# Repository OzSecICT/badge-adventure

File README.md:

# OzSec 2024 Adventure Badge

This repo contains the code and KiCad files to design the OzSec 2024 badge. 

## Theme

The theme of this year's badge is 'Light The Badge' where the front of the badge has LEDs representing various cities. In the default mode it will be twinkly and randomly blink the LEDs. 

When you connect to the badge via a serial console, a text-based adventure RPG will be playable. Each city in the game is represented by an LED, and each city will have a quest that needs to be completed. 

Once you complete each city's quest, that LED will light up. You need to light up every city in order to unlock access to Wichita and change the RGB LED. Completing that ultimate quest will reveal a CTF flag and change the RGB LED to green. 

## Codebase

The badge is based on an ESP32-S3 using the Arduino framework. This repo is designed to be opened in VS Code with the PlatformIO extension. 

### Files

Brief overview of the files and what they do:

**include/config.hpp:**
- Tracks the currently developed version for use with updates over the web. 
- WiFi SSID and Password defaults.

**include/ozsec/update.hpp and src/ozsec/update.cpp:**
- Manages over the air updates.
- Triggered by holding boot button in `main.cpp`

**includes/ozsec/ble.hpp and src/ozsec/ble.hpp:**
- Bluetooth Low Energy config, searches for an advertisement from an OzSec 2023: S1M0N badge. Sets a variable once a badge advertisement is found and stops searching.

**includes/ozsec/lights.hpp and src/ozsec/lights.cpp:**
- Manages the LEDs and NeoPixel RGB LED
- `Lights::twinkle()` is the main function that is called by `Adventure::bgloop()` on the second core in `main.cpp` to twinkle the lights when not in the game.

**src/main.cpp:**
- Main arduino `setup()` and `loop()` functions that call other class functions. 
- Sets up buttons using the OneButton library.
- Manages persistent data and game/badge states using the Preferences library.

**includes/ozsec/buttons.hpp:**
- Centralized setup of the buttons using OneButton

**includes/ozsec/rooms.hpp:**
- Room configs for the text based adventure

**includes/ozsec/npcs.hpp:**
- NPC config for the text based adventure

**includes/ozsec/adventure.hpp and src/ozsec/adventure.cpp:**
- The main text based adventure game.
- Manages character and badge states, what lights are lit, flags unlocked, etc.

### Wi-Fi setup
You can either set the wifi credentials in `config.hpp` or you can launch into the text game and enter `wifi` command to set it on your badge specifically.

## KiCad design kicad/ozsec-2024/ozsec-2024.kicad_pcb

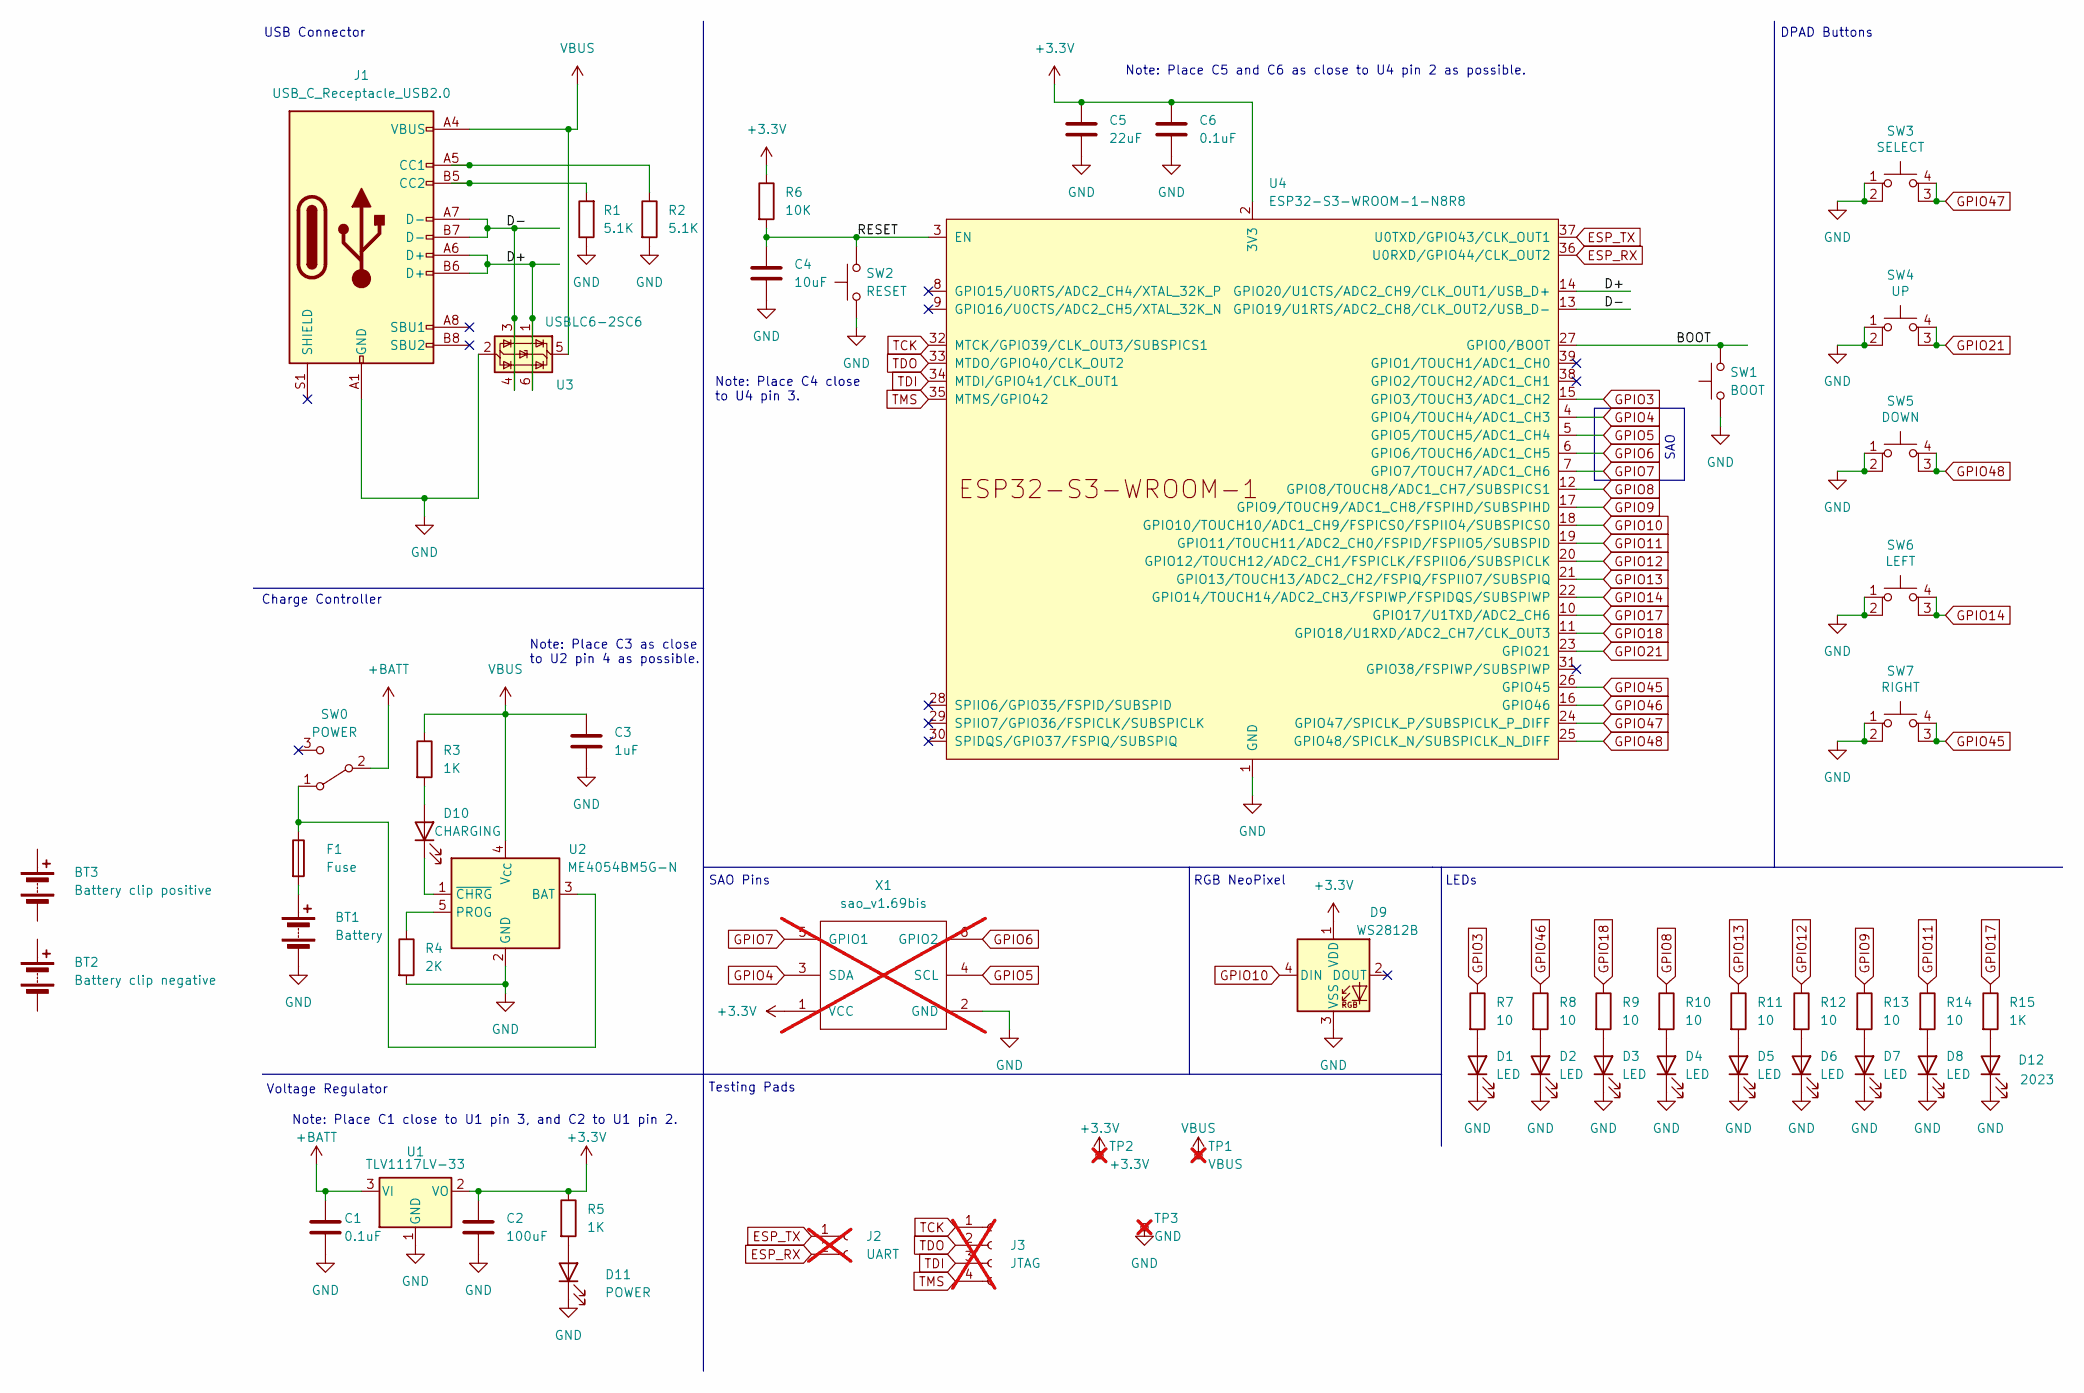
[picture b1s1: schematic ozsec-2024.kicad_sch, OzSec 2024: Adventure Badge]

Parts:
BT1: Battery; MY-AA-04_Silkscreen_Only; LCSC C2979179
BT2: Battery clip negative; MY-AA-04_Negative; LCSC C2979179
BT3: Battery clip positive; MY-AA-04_Positive; LCSC C2979179
C1, C6: 0.1uF; C_0402_1005Metric; LCSC C1525
C2: 100uF; C_1206_3216Metric; LCSC C15008
C3: 1uF; C_0402_1005Metric; LCSC C52923
C4: 10uF; C_0805_2012Metric; LCSC C15850
C5: 22uF; C_0805_2012Metric; LCSC C45783
D1, D2, D3, D4, D5, D6, D7, D8: LED; LED_0805_2012Metric_Pad1.15x1.40mm_HandSolder; LCSC C34499
D9: WS2812B; LED_WS2812B_PLCC4_5.0x5.0mm_P3.2mm; LCSC C2843785
D10: CHARGING; LED_0805_2012Metric_Pad1.15x1.40mm_HandSolder; LCSC C2296
D11: POWER; LED_0805_2012Metric_Pad1.15x1.40mm_HandSolder; LCSC C2297
D12: 2023; LED_0805_2012Metric_Pad1.15x1.40mm_HandSolder; LCSC C2297
F1: Fuse; Fuse_1206_3216Metric; LCSC C261957
J1: USB_C_Receptacle_USB2.0; USB_C_Receptacle_G-Switch_GT-USB-7010ASV; LCSC C2988369
J2: UART; PinHeader_1x02_P2.54mm_Vertical; not fitted
J3: JTAG; PinHeader_1x04_P2.54mm_Vertical; not fitted
R1, R2: 5.1K; R_0805_2012Metric; LCSC C27834
R3, R5, R15: 1K; R_0805_2012Metric_Pad1.20x1.40mm_HandSolder; LCSC C17513
R4: 2K; R_0805_2012Metric; LCSC C17604
R6: 10K; R_0805_2012Metric; LCSC C17414
R7, R8, R9, R10, R11, R12, R13, R14: 10; R_0805_2012Metric; LCSC C17415
SW0: POWER; SW_SPDT_PCM12; LCSC C431541
SW1: BOOT; SW_Push_1P1T_XKB_TS-1187A; LCSC C318884
SW2: RESET; SW_Push_1P1T_XKB_TS-1187A; LCSC C318884
SW3: SELECT; SW_SMD_TSC015XXXXXXX; LCSC C2888900
SW4: UP; SW_SMD_TSC015XXXXXXX; LCSC C2888900
SW5: DOWN; SW_SMD_TSC015XXXXXXX; LCSC C2888900
SW6: LEFT; SW_SMD_TSC015XXXXXXX; LCSC C2888900
SW7: RIGHT; SW_SMD_TSC015XXXXXXX; LCSC C2888900
TP1: VBUS; TestPoint_Pad_D1.5mm; not fitted
TP2: +3.3V; TestPoint_Pad_D1.5mm; not fitted
TP3: GND; TestPoint_Pad_1.5x1.5mm; not fitted
U1: TLV1117LV-33; SOT-223; LCSC C15578
U2: ME4054BM5G-N; TSOT-23-5; LCSC C478383
U3: USBLC6-2SC6; SOT-23-6; LCSC C2827654
U4: ESP32-S3-WROOM-1-N8R8; ESP32-S3-WROOM-1; LCSC C2913201
X1: sao_v1.69bis; Badgelife-SAOv169-BADGE-2x3; not fitted

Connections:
+3.3V: C2.1, C5.1, C6.1, D9.1 (VDD), R5.1, R6.1, TP2.1, U1.2 (VO), U1.4, U4.2 (3V3), X1.1 (VCC)
+BATT: C1.1, SW0.2 (B), U1.3 (VI)
/BOOT: SW1.2, U4.27 (GPIO0/BOOT)
/D+: J1.A6 (D+), J1.B6 (D+), U3.1 (I/O1), U3.6 (I/O1), U4.14 (GPIO20/U1CTS/ADC2_CH9/CLK_OUT1/USB_D+)
/D-: J1.A7 (D-), J1.B7 (D-), U3.3 (I/O2), U3.4 (I/O2), U4.13 (GPIO19/U1RTS/ADC2_CH8/CLK_OUT2/USB_D-)
/RESET: C4.1, R6.2, SW2.2, U4.3 (EN)
ESP_RX: J2.2, U4.36 (U0RXD/GPIO44/CLK_OUT2)
ESP_TX: J2.1, U4.37 (U0TXD/GPIO43/CLK_OUT1)
GND: BT1.2 (-), BT2.2 (-), C1.2, C2.2, C3.2, C4.2, C5.2, C6.2, D1.1 (K), D2.1 (K), D3.1 (K), D4.1 (K), D5.1 (K), D6.1 (K), D7.1 (K), D8.1 (K), D9.3 (VSS), D11.1 (K), D12.1 (K), J1.A1 (GND), J1.A12 (GND), J1.B1 (GND), J1.B12 (GND), R1.1, R2.2, R4.2, SW1.1, SW2.1, SW3.1, SW3.2, SW4.1, SW4.2, SW5.1, SW5.2, SW6.1, SW6.2, SW7.1, SW7.2, TP3.1, U1.1 (GND), U2.2 (GND), U3.2 (GND), U4.1 (GND), U4.40 (GND), U4.41 (GND), X1.2 (GND)
GPIO3: R7.1, U4.15 (GPIO3/TOUCH3/ADC1_CH2)
GPIO4: U4.4 (GPIO4/TOUCH4/ADC1_CH3), X1.3 (SDA)
GPIO5: U4.5 (GPIO5/TOUCH5/ADC1_CH4), X1.4 (SCL)
GPIO6: U4.6 (GPIO6/TOUCH6/ADC1_CH5), X1.6 (GPIO2)
GPIO7: U4.7 (GPIO7/TOUCH7/ADC1_CH6), X1.5 (GPIO1)
GPIO8: R10.1, U4.12 (GPIO8/TOUCH8/ADC1_CH7/SUBSPICS1)
GPIO9: R13.1, U4.17 (GPIO9/TOUCH9/ADC1_CH8/FSPIHD/SUBSPIHD)
GPIO10: D9.4 (DIN), U4.18 (GPIO10/TOUCH10/ADC1_CH9/FSPICS0/FSPIIO4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)
GPIO11: R14.1, U4.19 (GPIO11/TOUCH11/ADC2_CH0/FSPID/FSPIIO5/S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)
GPIO12: R12.1, U4.20 (GPIO12/TOUCH12/ADC2_CH1/FSPICLK/FSPIIO6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)
GPIO13: R11.1, U4.21 (GPIO13/TOUCH13/ADC2_CH2/FSPIQ/FSPIIO7/S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)
GPIO14: SW6.3 (K), SW6.4 (A), U4.22 (GPIO14/TOUCH14/ADC2_CH3/FSPIWP/FSPIDQS/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)
GPIO17: R15.1, U4.10 (GPIO17/U1TXD/ADC2_CH6)
GPIO18: R9.1, U4.11 (GPIO18/U1RXD/ADC2_CH7/CLK_OUT3)
GPIO21: SW4.3 (K), SW4.4 (A), U4.23 (GPIO21)
GPIO45: SW7.3 (K), SW7.4 (A), U4.26 (GPIO45)
GPIO46: R8.1, U4.16 (GPIO46)
GPIO47: SW3.3 (K), SW3.4 (A), U4.24 (GPIO47/SPICLK_P/SUBSPICLK_P_DIFF)
GPIO48: SW5.3 (K), SW5.4 (A), U4.25 (GPIO48/SPICLK_N/SUBSPICLK_N_DIFF)
unnamed: D1.2 (A), R7.2
unnamed: D2.2 (A), R8.2
unnamed: D3.2 (A), R9.2
unnamed: D4.2 (A), R10.2
unnamed: D5.2 (A), R11.2
unnamed: D6.2 (A), R12.2
unnamed: D7.2 (A), R13.2
unnamed: D8.2 (A), R14.2
unnamed: D10.2 (A), R3.2
unnamed: D10.1 (K), U2.1 (~CHRG)
unnamed: D11.2 (A), R5.2
unnamed: D12.2 (A), R15.2
unnamed: J1.A5 (CC1), R2.1
unnamed: J1.B5 (CC2), R1.2
unnamed: F1.1, SW0.1 (A), U2.3 (BAT)
unnamed: R4.1, U2.5 (PROG)
TCK: J3.1, U4.32 (MTCK/GPIO39/CLK_OUT3/SUBSPICS1)
TDI: J3.3, U4.34 (MTDI/GPIO41/CLK_OUT1)
TDO: J3.2, U4.33 (MTDO/GPIO40/CLK_OUT2)
TMS: J3.4, U4.35 (MTMS/GPIO42)
VBUS: C3.1, J1.A4 (VBUS), J1.A9 (VBUS), J1.B4 (VBUS), J1.B9 (VBUS), R3.1, TP1.1, U2.4 (V_{CC}), U3.5 (VBUS)

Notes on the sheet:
Testing Pads
USB Connector
Note: Place C5 and C6 as close to U4 pin 2 as possible.
DPAD Buttons
Voltage Regulator
SAO
Note: Place C3 as close to U2 pin 4 as possible.
Note: Place C4 close to U4 pin 3.
RGB NeoPixel
SAO Pins
Charge Controller
Note: Place C1 close to U1 pin 3, and C2 to U1 pin 2.
LEDs

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
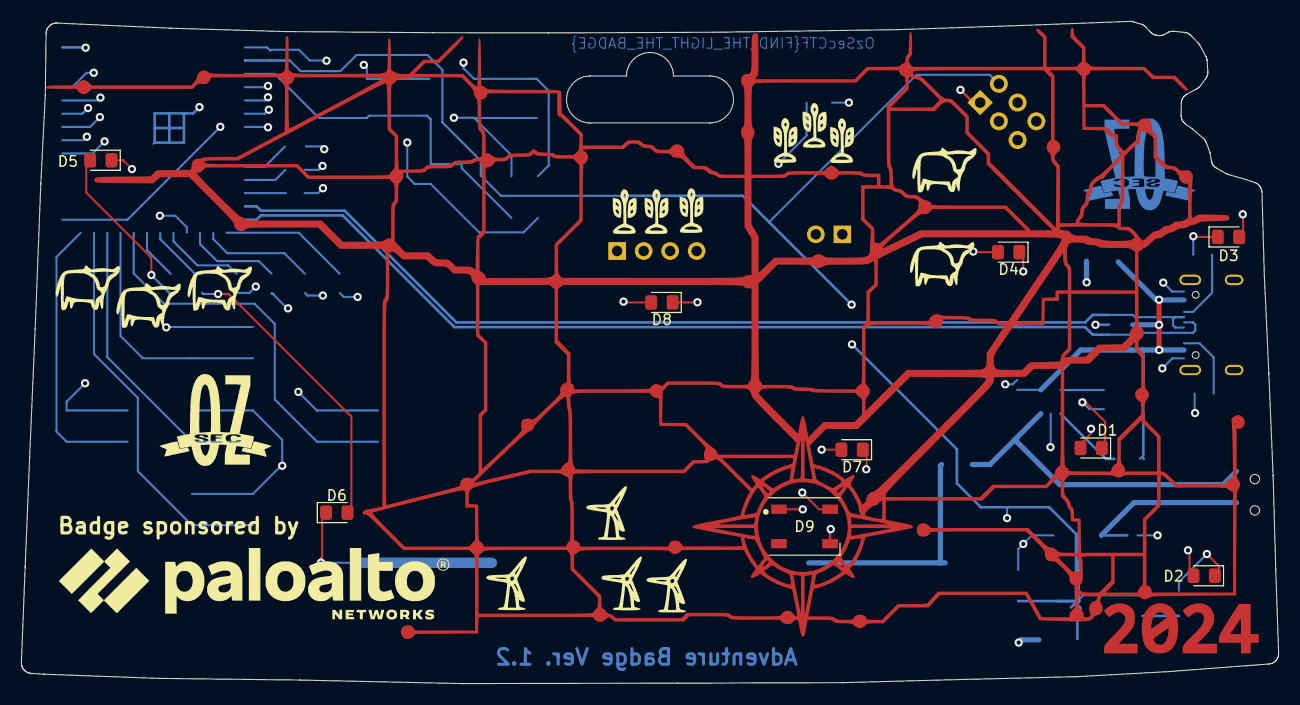
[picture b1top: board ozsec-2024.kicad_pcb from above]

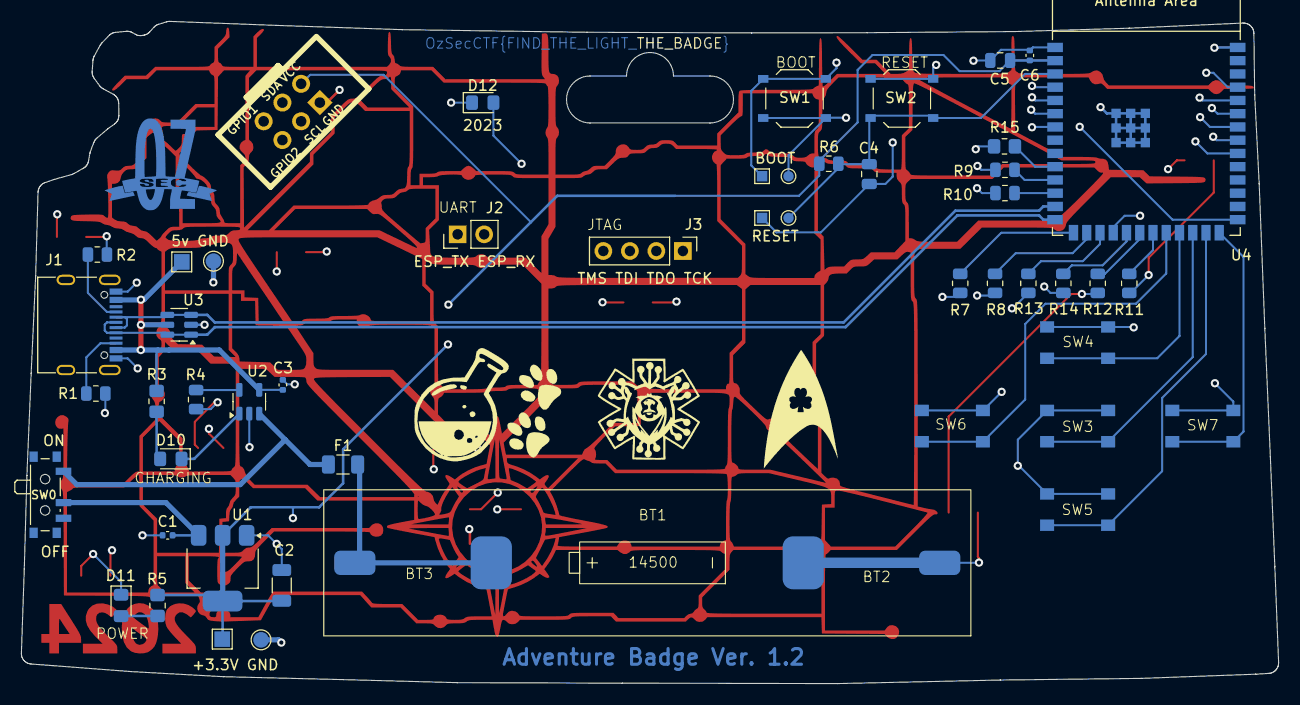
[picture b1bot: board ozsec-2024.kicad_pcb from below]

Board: 4 copper layers, 120.5 x 63.5 mm, 53 parts (43 on the bottom side), 50 nets.

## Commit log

2024-10-20 Added firmware.
2024-10-20 Updated firmware.
2024-10-20 Added kicad files.
2024-10-24 Added source code.
2024-10-24 Added bundled firmware file.
2024-10-24 Guide updates.
2024-10-24 Update.
2024-10-24 Updates to guide.
